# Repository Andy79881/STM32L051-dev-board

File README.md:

# STM32L051-dev-board
### ***A small-footprint, custom development PCB for the STM32L051C8Tx***

* This board's MCU is an Access line ultra low power STM32L051C8T6 with 64 kB of flash, 8 kB of SRAM and an ARM Cortex-M0+ core in a 48-pin LQFP package.

* The board supports I<sup>2</sup>C, SPI and UART as communication interfaces. Checkout the datasheet for details.
* Flashing and In-Circuit-Debugging can be achieved through an ST-LINK V3 Mini external flasher / debugger using the SWD protocol. The development board provides an 14 pin connector with 1.27mm pitch (J1) for direct connection to the ST-Link V3 Mini via STDC14 flat
cable. USART2 is available on connector J1 as well. Alternatively, any other suitable programmer can be connected via P1 and jumper wires.
* The board is powered via VPP (+5V) and draws very little current. Power conversion occurs through an onboard 5~3.3V linear regulator.
* The board has a 32.768 kHz clock for RTC capabilities as well as an 8.000 MHz system clock. It also features an indicator LED together with an open collector stage to drive higher current load (both assigned at PC13), a reset button and a boot select jumper.
* The footprint of the board is 32x54 mm and its 2.54 mm pitch headers allow it to be used with standard breadboards.

---

**I/O connectors (J2, J4) Pinout 1)**

<table>
<tr>
<th>J2</th>
<th>J4</th>
</tr>
<tr>

<td>

| Pin no | Pin name  |
|--------|-----------|
| 1      | GND       |
| 2      | Load 2)   |
| 3      | PA0       |
| 4      | PA1       |
| 5      | PA4       |
| 6      | PA5       |
| 7      | PA6       |
| 8      | PA7       |
| 9      | PB0       |
| 10     | PB1       |
| 11     | PB2       |
| 12     | PB10      |
| 13     | PB11      |
| 14     | PB12      |
| 15     | PB13      |
| 16     | PB14      |

</td><td>

| Pin no | Pin name  |
|--------|-----------|
| 1      | PB9       |
| 2      | PB8       |
| 3      | PB7       |
| 4      | PB6       |
| 5      | PB5       |
| 6      | PB4       |
| 7      | PB3       |
| 8      | PA15      |
| 9      | PA12      |
| 10     | PA11      |
| 11     | PA10      |
| 12     | PA9       |
| 13     | PA8       |
| 14     | PB15      |
| 15     | GND       |
| 16     | VPP (+5V) |

</td></tr> </table>

**Notes:**
1. J2 left, J4 right for PCB front view
2. PC13 assigned to open collector output and built-in LED 

| Front view | Rear view |
|------------|-----------|
|            |           |

SWD debug / programming connector for ST-link V3 mini highlighted.

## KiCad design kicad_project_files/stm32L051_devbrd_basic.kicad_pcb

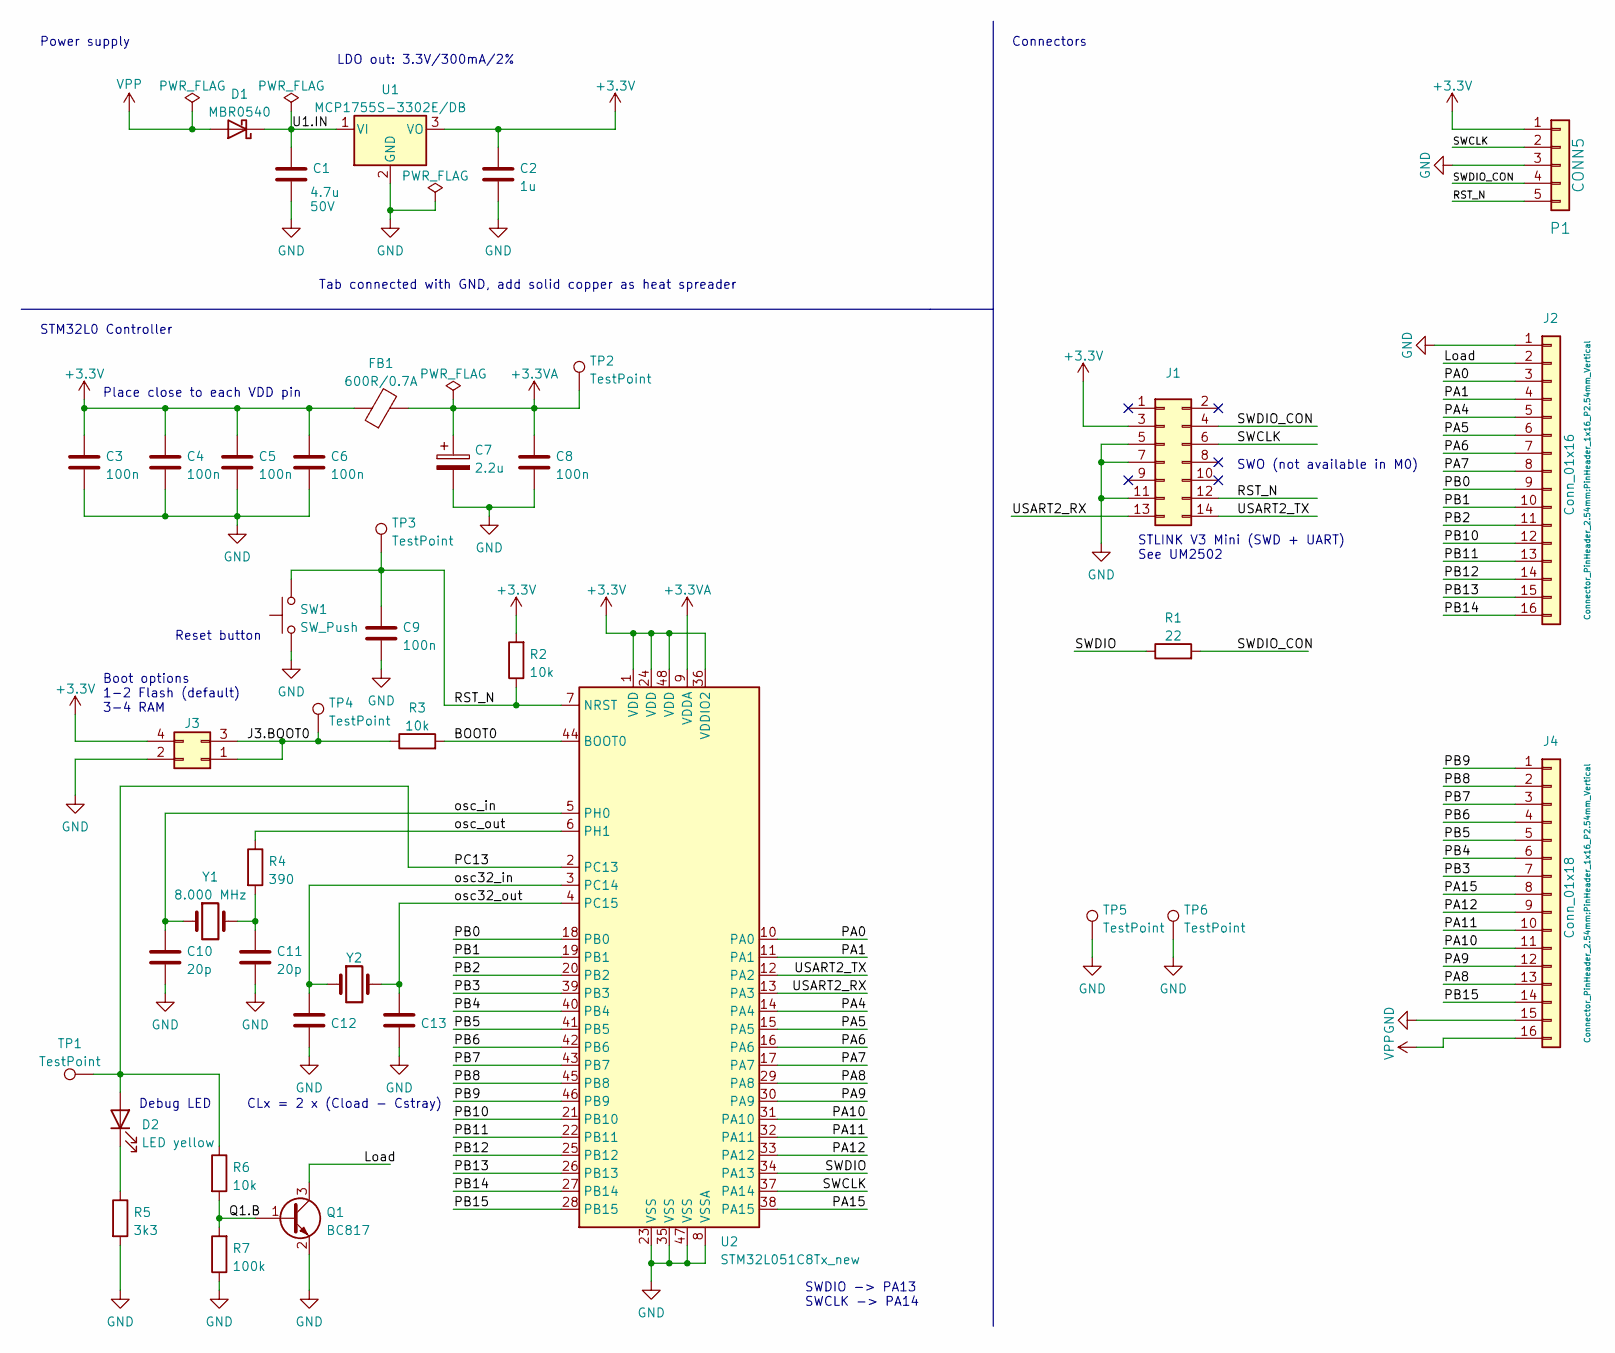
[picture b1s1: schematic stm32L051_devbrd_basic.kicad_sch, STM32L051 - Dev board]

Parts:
C1: 4.7u; C_1210_3225Metric_Pad1.33x2.70mm_HandSolder
C2: 1u; C_0805_2012Metric_Pad1.18x1.45mm_HandSolder
C3, C4, C5, C6, C8, C9: 100n; C_0805_2012Metric_Pad1.18x1.45mm_HandSolder
C7: 2.2u; CP_Elec_4x5.8
C10, C11: 20p; C_0603_1608Metric
C12, C13: 10p; C_0603_1608Metric
D1: MBR0540; D_SOD-123
D2: LED yellow; LED_0805_2012Metric_Pad1.15x1.40mm_HandSolder
FB1: 600R/0.7A; L_0805_2012Metric_Pad1.05x1.20mm_HandSolder
J1: Conn_02x07_Odd_Even; PinHeader_2x07_P1.27mm_Vertical
J2: Conn_01x16; PinHeader_1x16_P2.54mm_Vertical
J3: Conn_02x02_Odd_Even; PinHeader_2x02_P2.54mm_Vertical
J4: Conn_01x18; PinHeader_1x16_P2.54mm_Vertical
P1: CONN5; PinHeader_1x05_P2.54mm_Horizontal
Q1: BC817; SOT-23
R1: 22; R_0805_2012Metric_Pad1.20x1.40mm_HandSolder
R2, R3, R6: 10k; R_0805_2012Metric_Pad1.20x1.40mm_HandSolder
R4: 390; R_0805_2012Metric_Pad1.20x1.40mm_HandSolder
R5: 3k3; R_0805_2012Metric_Pad1.20x1.40mm_HandSolder
R7: 100k; R_0805_2012Metric_Pad1.20x1.40mm_HandSolder
SW1: SW_Push; SW_SPST_B3S-1000
TP1, TP2, TP3, TP4: TestPoint; TestPoint_Pad_D1.0mm
TP5, TP6: TestPoint; TestPoint_Keystone_5000-5004_Miniature
U1: MCP1755S-3302E/DB; SOT-223-3_TabPin2
U2: STM32L051C8Tx_new; LQFP-48_7x7mm_P0.5mm
Y1: 8.000 MHz; Crystal_SMD_HC49-SD
Y2: 32.768kHz; Crystal_SMD_3215-2Pin_3.2x1.5mm

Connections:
+3.3V: C2.1, C3.1, C4.1, C5.1, C6.1, FB1.1, J1.3, J3.4, P1.1, R2.2, U1.3 (VO), U2.1 (VDD), U2.24 (VDD), U2.36 (VDDIO2), U2.48 (VDD)
+3.3VA: C7.1, C8.1, FB1.2, TP2.1, U2.9 (VDDA)
/BOOT0: R3.2, U2.44 (BOOT0)
/J3.BOOT0: J3.1, J3.3, R3.1, TP4.1
/Load: J2.2, Q1.3 (C)
/PA0: J2.3, U2.10 (PA0)
/PA1: J2.4, U2.11 (PA1)
/PA4: J2.5, U2.14 (PA4)
/PA5: J2.6, U2.15 (PA5)
/PA6: J2.7, U2.16 (PA6)
/PA7: J2.8, U2.17 (PA7)
/PA8: J4.13, U2.29 (PA8)
/PA9: J4.12, U2.30 (PA9)
/PA10: J4.11, U2.31 (PA10)
/PA11: J4.10, U2.32 (PA11)
/PA12: J4.9, U2.33 (PA12)
/PA15: J4.8, U2.38 (PA15)
/PB0: J2.9, U2.18 (PB0)
/PB1: J2.10, U2.19 (PB1)
/PB2: J2.11, U2.20 (PB2)
/PB3: J4.7, U2.39 (PB3)
/PB4: J4.6, U2.40 (PB4)
/PB5: J4.5, U2.41 (PB5)
/PB6: J4.4, U2.42 (PB6)
/PB7: J4.3, U2.43 (PB7)
/PB8: J4.2, U2.45 (PB8)
/PB9: J4.1, U2.46 (PB9)
/PB10: J2.12, U2.21 (PB10)
/PB11: J2.13, U2.22 (PB11)
/PB12: J2.14, U2.25 (PB12)
/PB13: J2.15, U2.26 (PB13)
/PB14: J2.16, U2.27 (PB14)
/PB15: J4.14, U2.28 (PB15)
/PC13: D2.2 (A), R6.1, TP1.1, U2.2 (PC13)
/Q1.B: Q1.1 (B), R6.2, R7.2
/RST_N: C9.1, J1.12, P1.5, R2.1, SW1.2, TP3.1, U2.7 (NRST)
/SWCLK: J1.6, P1.2, U2.37 (PA14)
/SWDIO: R1.1, U2.34 (PA13)
/SWDIO_CON: J1.4, P1.4, R1.2
/U1.IN: C1.1, D1.1 (K), U1.1 (VI)
/USART2_RX: J1.13, U2.13 (PA3)
/USART2_TX: J1.14, U2.12 (PA2)
/osc32_in: C12.1, U2.3 (PC14), Y2.1
/osc32_out: C13.1, U2.4 (PC15), Y2.2
/osc_in: C10.1, U2.5 (PH0), Y1.1
/osc_out: R4.1, U2.6 (PH1)
GND: C1.2, C2.2, C3.2, C4.2, C5.2, C6.2, C7.2, C8.2, C9.2, C10.2, C11.2, C12.2, C13.2, J1.5, J1.7, J1.11, J2.1, J3.2, J4.15, P1.3, Q1.2 (E), R5.2, R7.1, SW1.1, TP5.1, TP6.1, U1.2 (GND), U2.8 (VSSA), U2.23 (VSS), U2.35 (VSS), U2.47 (VSS)
unnamed: C11.1, R4.2, Y1.2
unnamed: D2.1 (K), R5.1
VPP: D1.2 (A), J4.16

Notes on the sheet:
CLx = 2 x (Cload - Cstray)
Boot options 1-2 Flash (default) 3-4 RAM
Tab connected with GND, add solid copper as heat spreader
Place close to each VDD pin
STLINK V3 Mini (SWD + UART) See UM2502
SWDIO -> PA13 SWCLK -> PA14
Connectors
LDO out: 3.3V/300mA/2%
Debug LED
Power supply
SWO (not available in M0)
Reset button
STM32L0 Controller

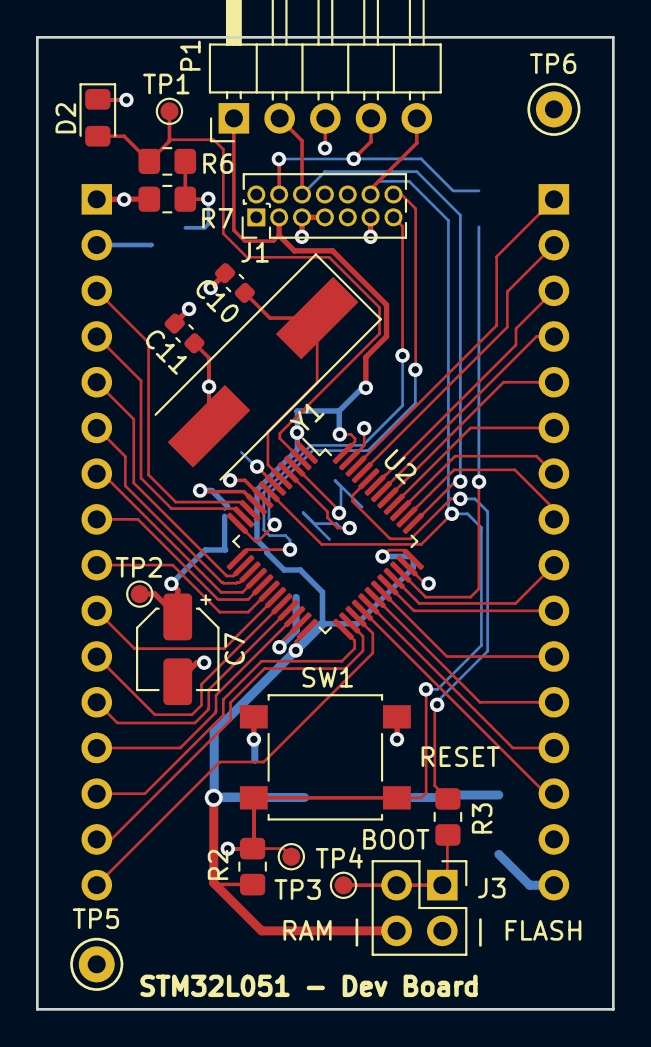
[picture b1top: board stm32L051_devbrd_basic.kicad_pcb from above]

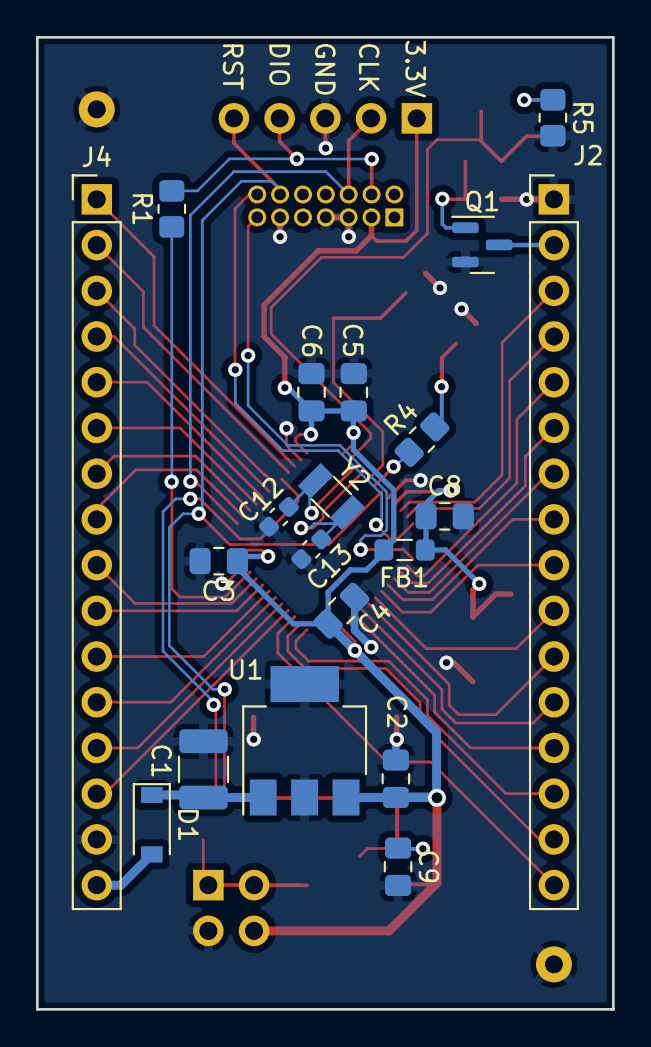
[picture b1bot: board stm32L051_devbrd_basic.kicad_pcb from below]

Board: 2 copper layers, 32.0 x 54.0 mm, 40 parts (20 on the bottom side), 50 nets.

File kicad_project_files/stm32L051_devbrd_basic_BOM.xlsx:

Id | Designator | Package | Quantity | Designation | Supplier and ref
1 | P1 | PinHeader_1x05_P2.54mm_Horizontal | 1 | CONN5
2 | D2 | LED_0805_2012Metric_Pad1.15x1.40mm_HandSolder | 1 | LED yellow
3 | TP4,TP3,TP2,TP1 | TestPoint_Pad_D1.0mm | 4 | TestPoint
4 | J1 | PinHeader_2x07_P1.27mm_Vertical | 1 | Conn_02x07_Odd_Even
5 | J3 | PinHeader_2x02_P2.54mm_Vertical | 1 | Conn_02x02_Odd_Even
6 | TP5,TP6 | TestPoint_Keystone_5000-5004_Miniature | 2 | TestPoint
7 | R3,R6,R2 | R_0805_2012Metric_Pad1.20x1.40mm_HandSolder | 3 | 10k
8 | Y1 | Crystal_SMD_HC49-SD | 1 | 8.000 MHz
9 | U2 | LQFP-48_7x7mm_P0.5mm | 1 | STM32L051C8Tx_new
10 | SW1 | SW_SPST_B3S-1000 | 1 | SW_Push
11 | C10,C11 | C_0603_1608Metric | 2 | 20p
12 | C7 | CP_Elec_4x5.8 | 1 | 2.2u
13 | R7 | R_0805_2012Metric_Pad1.20x1.40mm_HandSolder | 1 | 100k
14 | R5 | R_0805_2012Metric_Pad1.20x1.40mm_HandSolder | 1 | 3k3
15 | C1 | C_1210_3225Metric_Pad1.33x2.70mm_HandSolder | 1 | 4.7u
16 | Q1 | SOT-23 | 1 | BC817
17 | C3,C9,C6,C5,C8,C4 | C_0805_2012Metric_Pad1.18x1.45mm_HandSolder | 6 | 100n
18 | Y2 | Crystal_SMD_3215-2Pin_3.2x1.5mm | 1 | 32.768kHz
19 | J2 | PinHeader_1x16_P2.54mm_Vertical | 1 | Conn_01x16
20 | R4 | R_0805_2012Metric_Pad1.20x1.40mm_HandSolder | 1 | 390
21 | C2 | C_0805_2012Metric_Pad1.18x1.45mm_HandSolder | 1 | 1u
22 | R1 | R_0805_2012Metric_Pad1.20x1.40mm_HandSolder | 1 | 22
23 | J4 | PinHeader_1x16_P2.54mm_Vertical | 1 | Conn_01x18
24 | U1 | SOT-223-3_TabPin2 | 1 | MCP1755S-3302E/DB
25 | FB1 | L_0805_2012Metric_Pad1.05x1.20mm_HandSolder | 1 | 600R/0.7A
26 | C13,C12 | C_0603_1608Metric | 2 | 10p
27 | D1 | D_SOD-123 | 1 | MBR0540

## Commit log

2022-11-14 Update README.md
    IO connector tables for J2, J4 side by side. Refer to https://towardsdatascience.com/the-ultimate-markdown-cheat-sheet-3d3976b31a0
2022-11-14 Update README.md
    updated version: figures added, wording updated, notes added/ updated, layout improved
2022-11-21 Add files via upload
    Initial file upload of Kicad project
